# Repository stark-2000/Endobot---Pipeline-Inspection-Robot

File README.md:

Endobot 2.0, a tethered pipeline inspection robot which can detect leaks, corrosion and defects on pipelines as small as 4 inch up-to a depth of 300 meters and can withstand 5 bar underwater pressure.
It uses RS422 long distance data transfer protocol for camera feed & data transfer. The robot can be fully controlled from outside the pipeline using sophisticated controllers which enable 4 wheel drive and advanced transmission. 
Onboard IMU & Encoders enable accurate localisation & distance calculation of the robot. Realtime motor temp, indoor temp, pipeline leak sounds, current consumption, inclination calculation is all performed and displayed on a mini LCD screen.

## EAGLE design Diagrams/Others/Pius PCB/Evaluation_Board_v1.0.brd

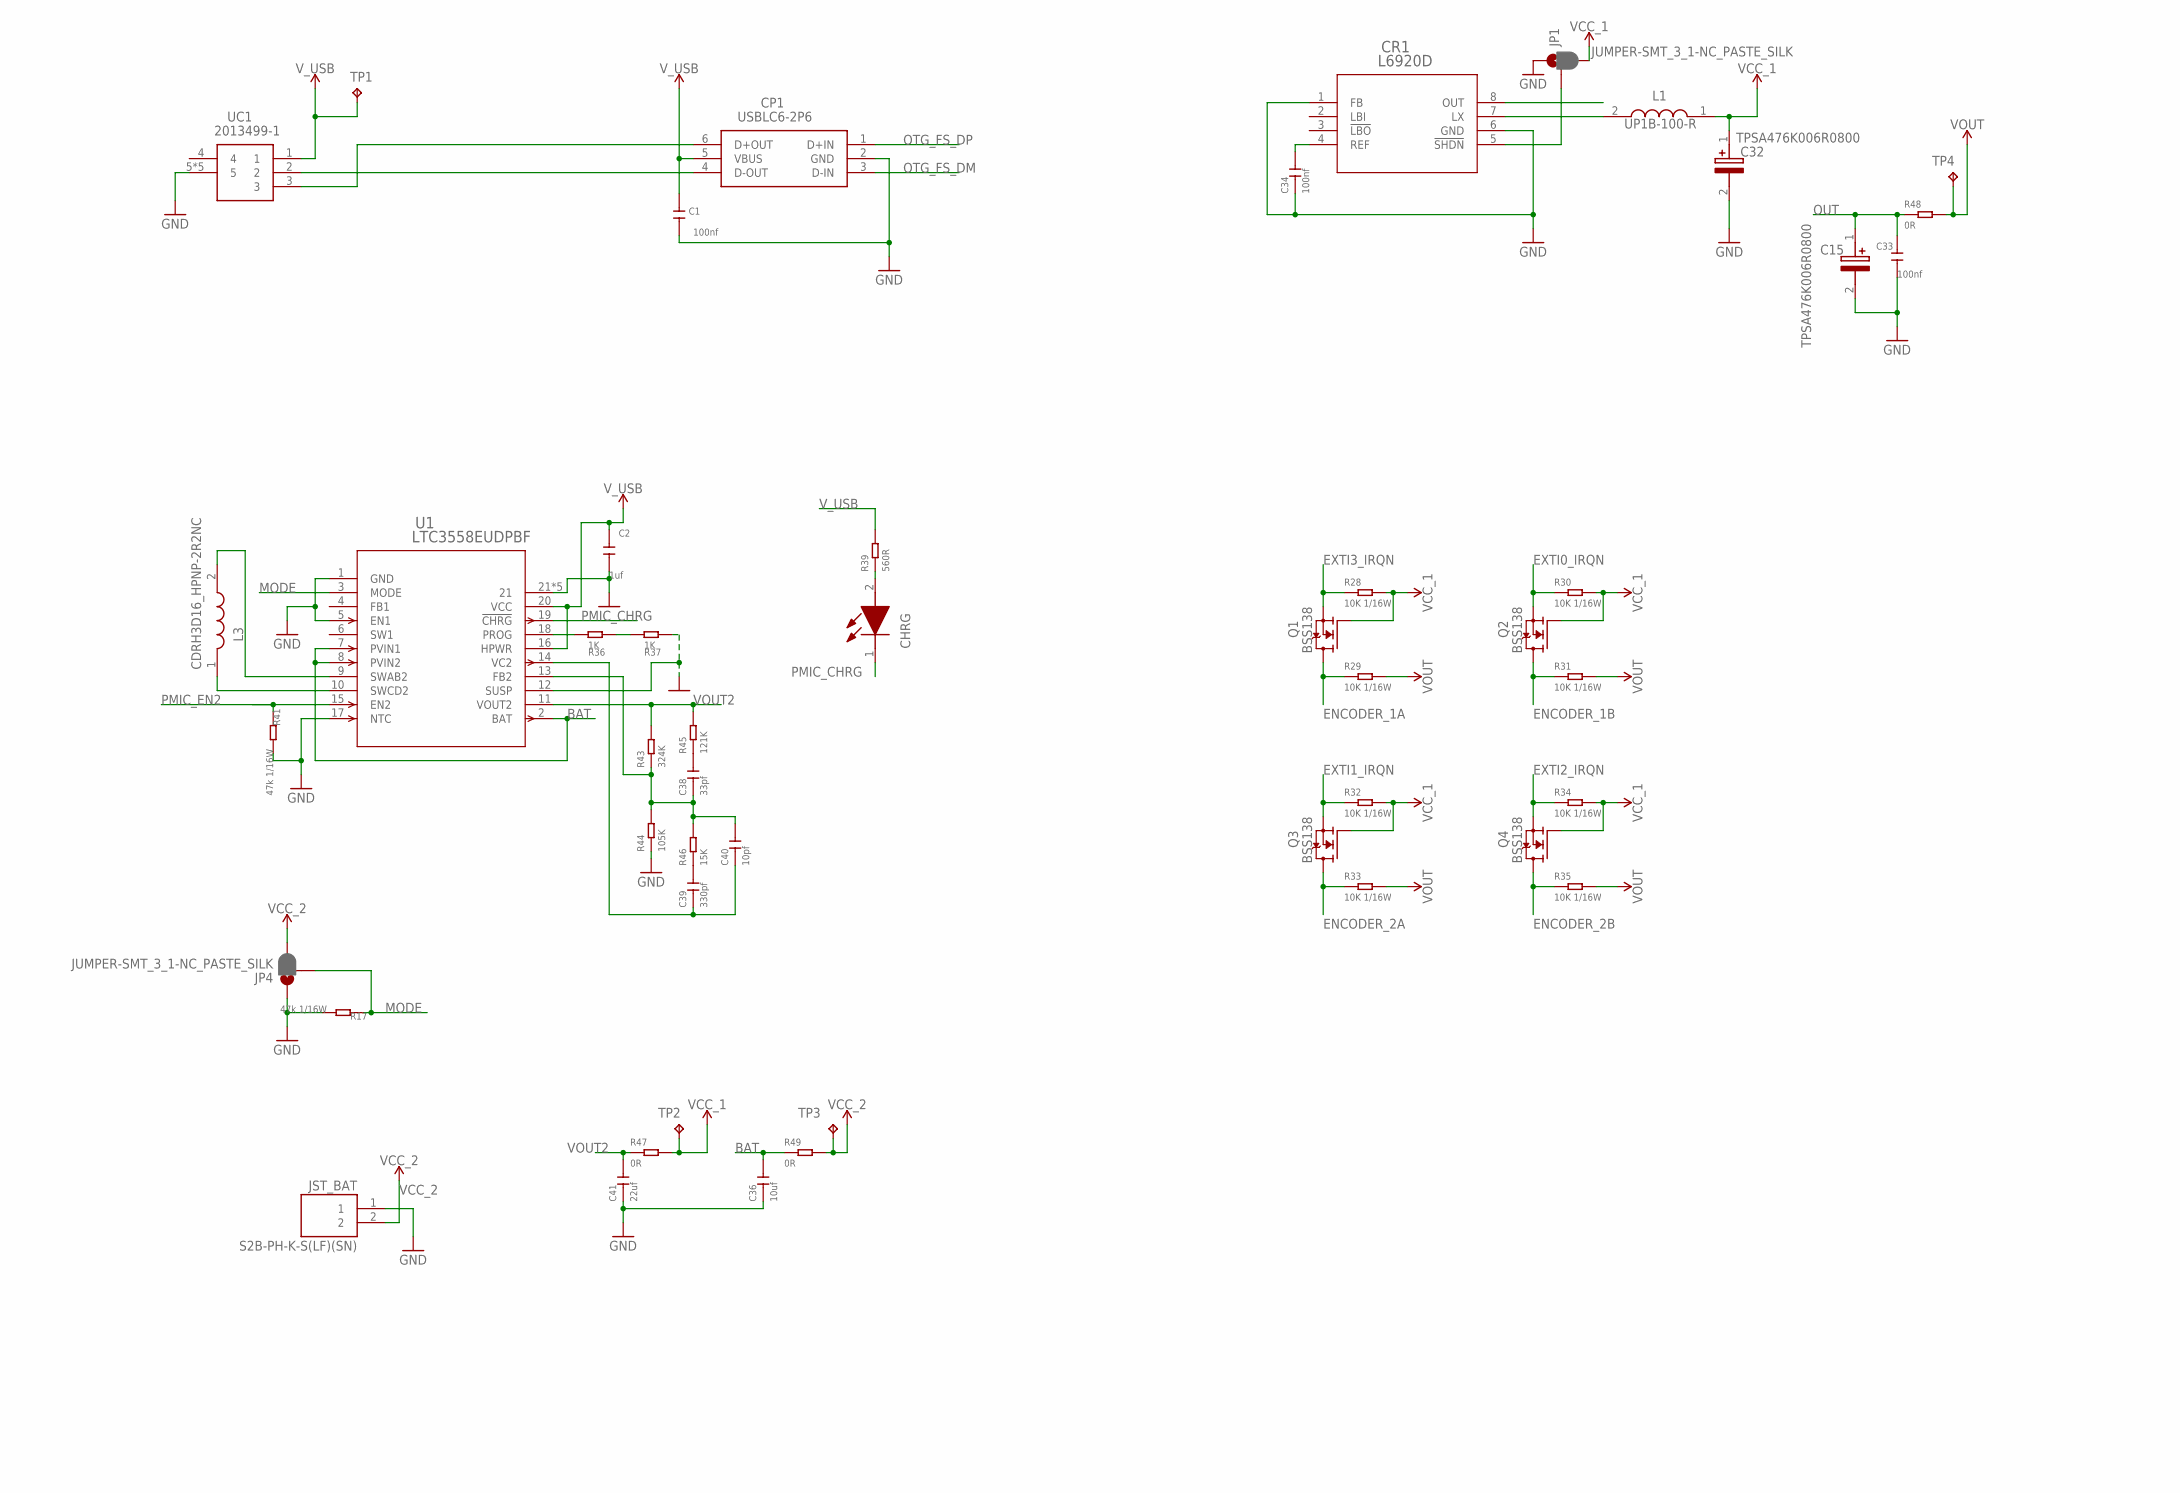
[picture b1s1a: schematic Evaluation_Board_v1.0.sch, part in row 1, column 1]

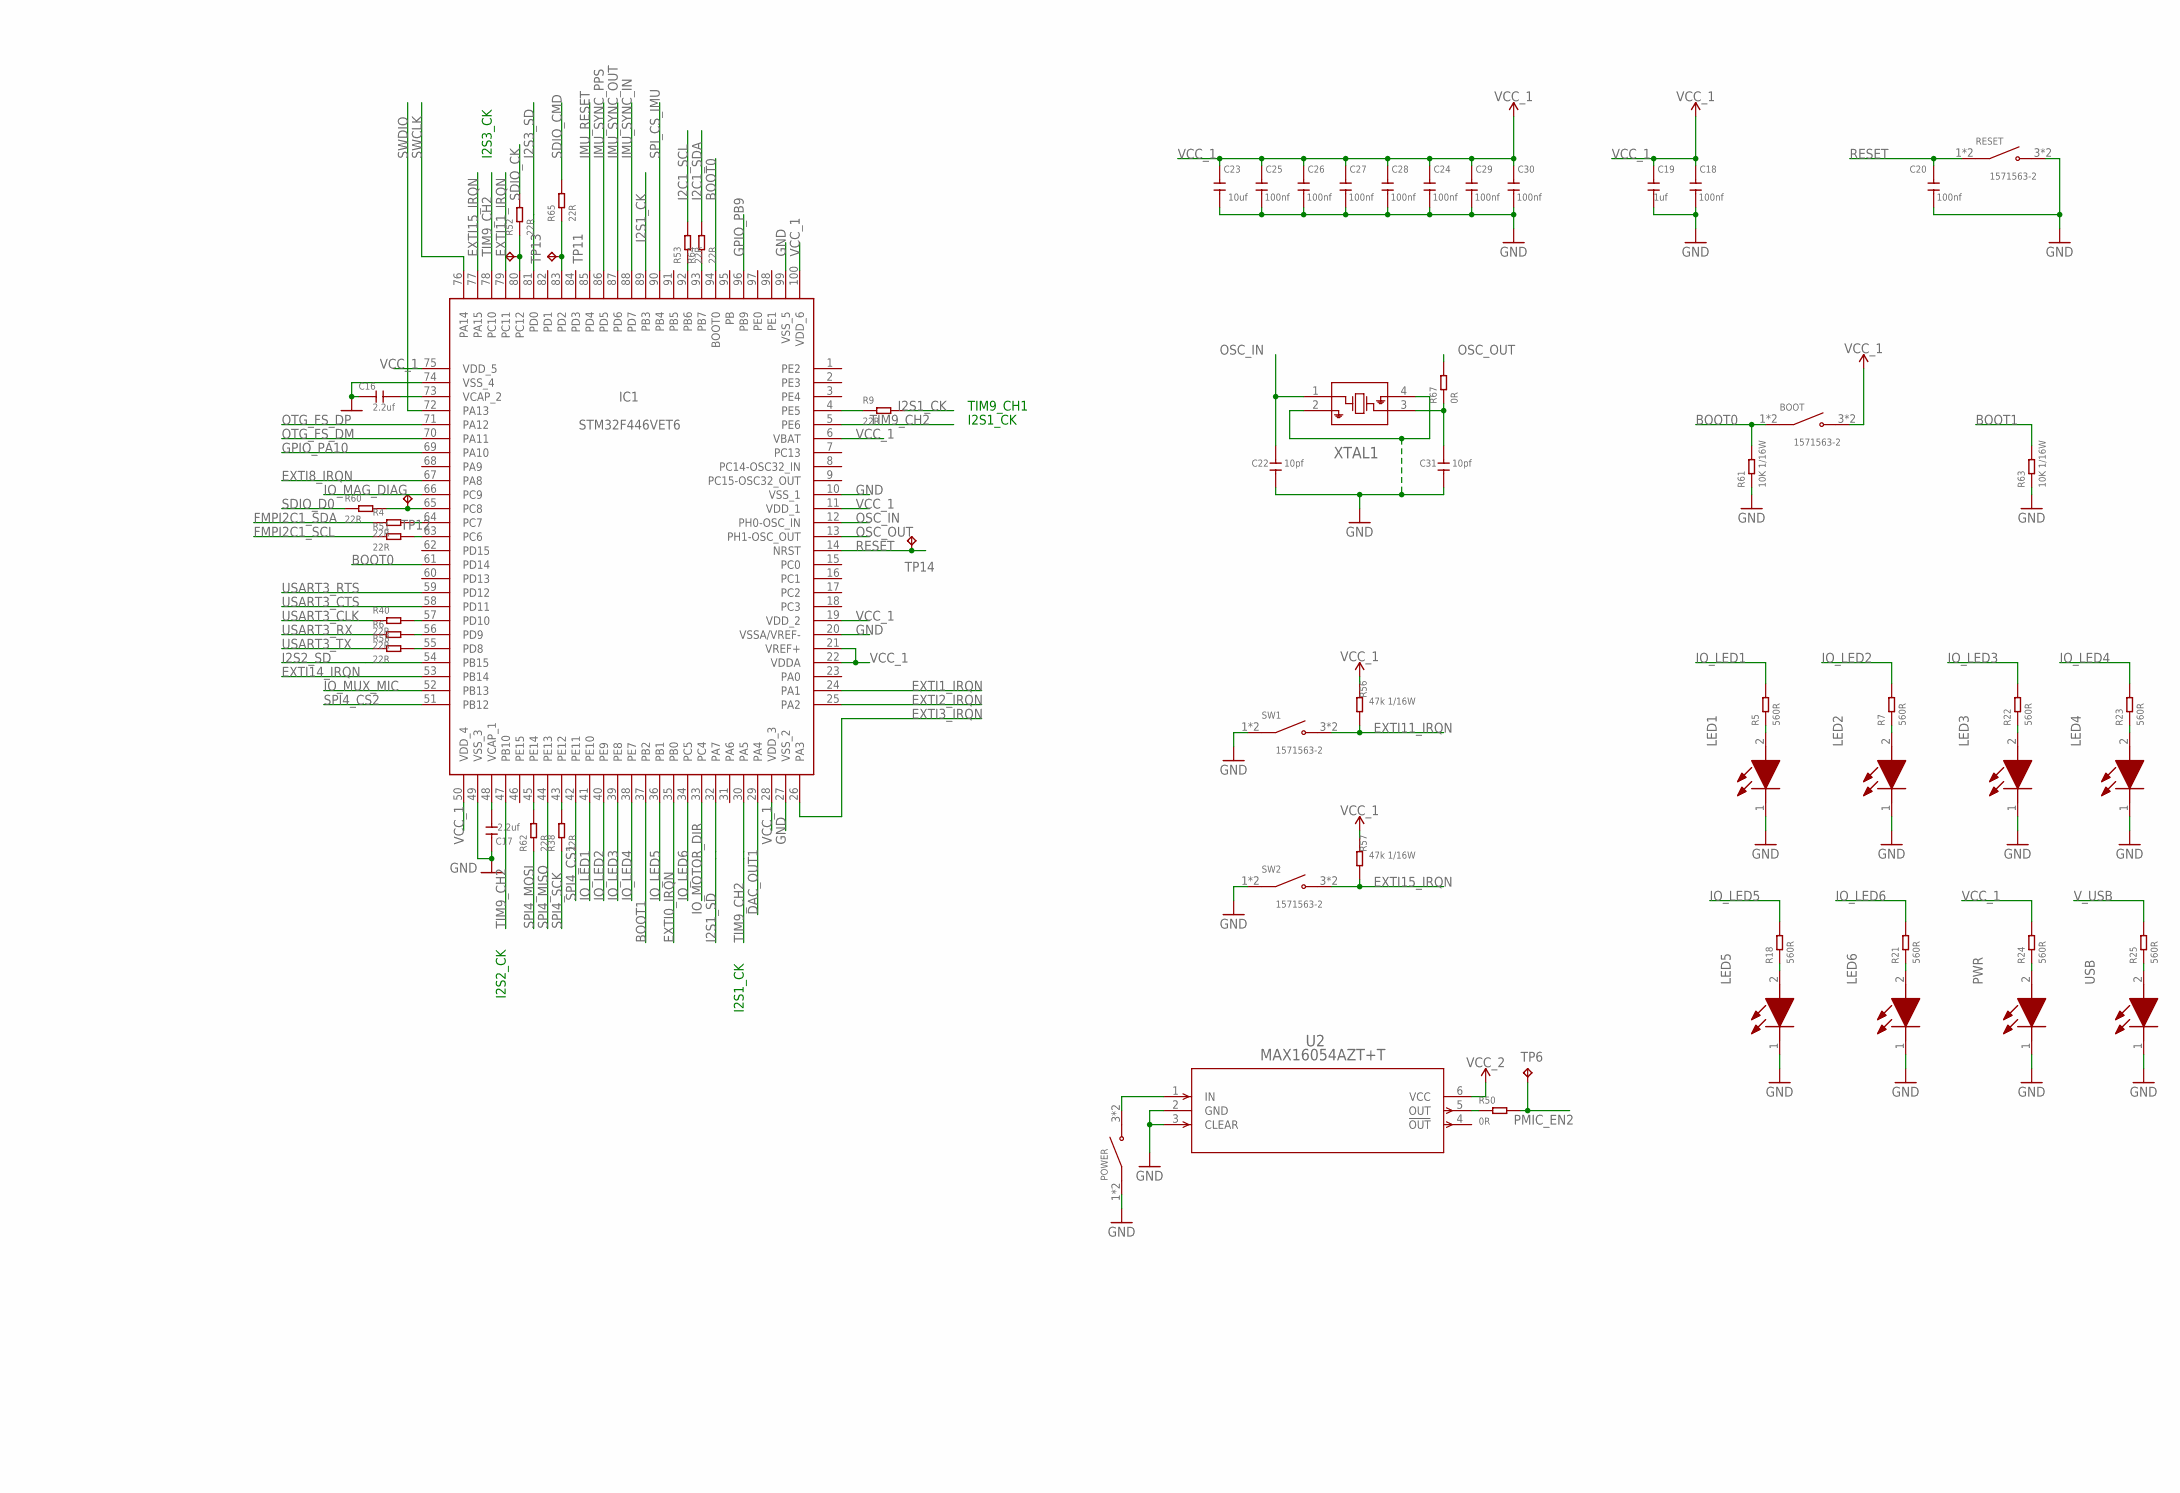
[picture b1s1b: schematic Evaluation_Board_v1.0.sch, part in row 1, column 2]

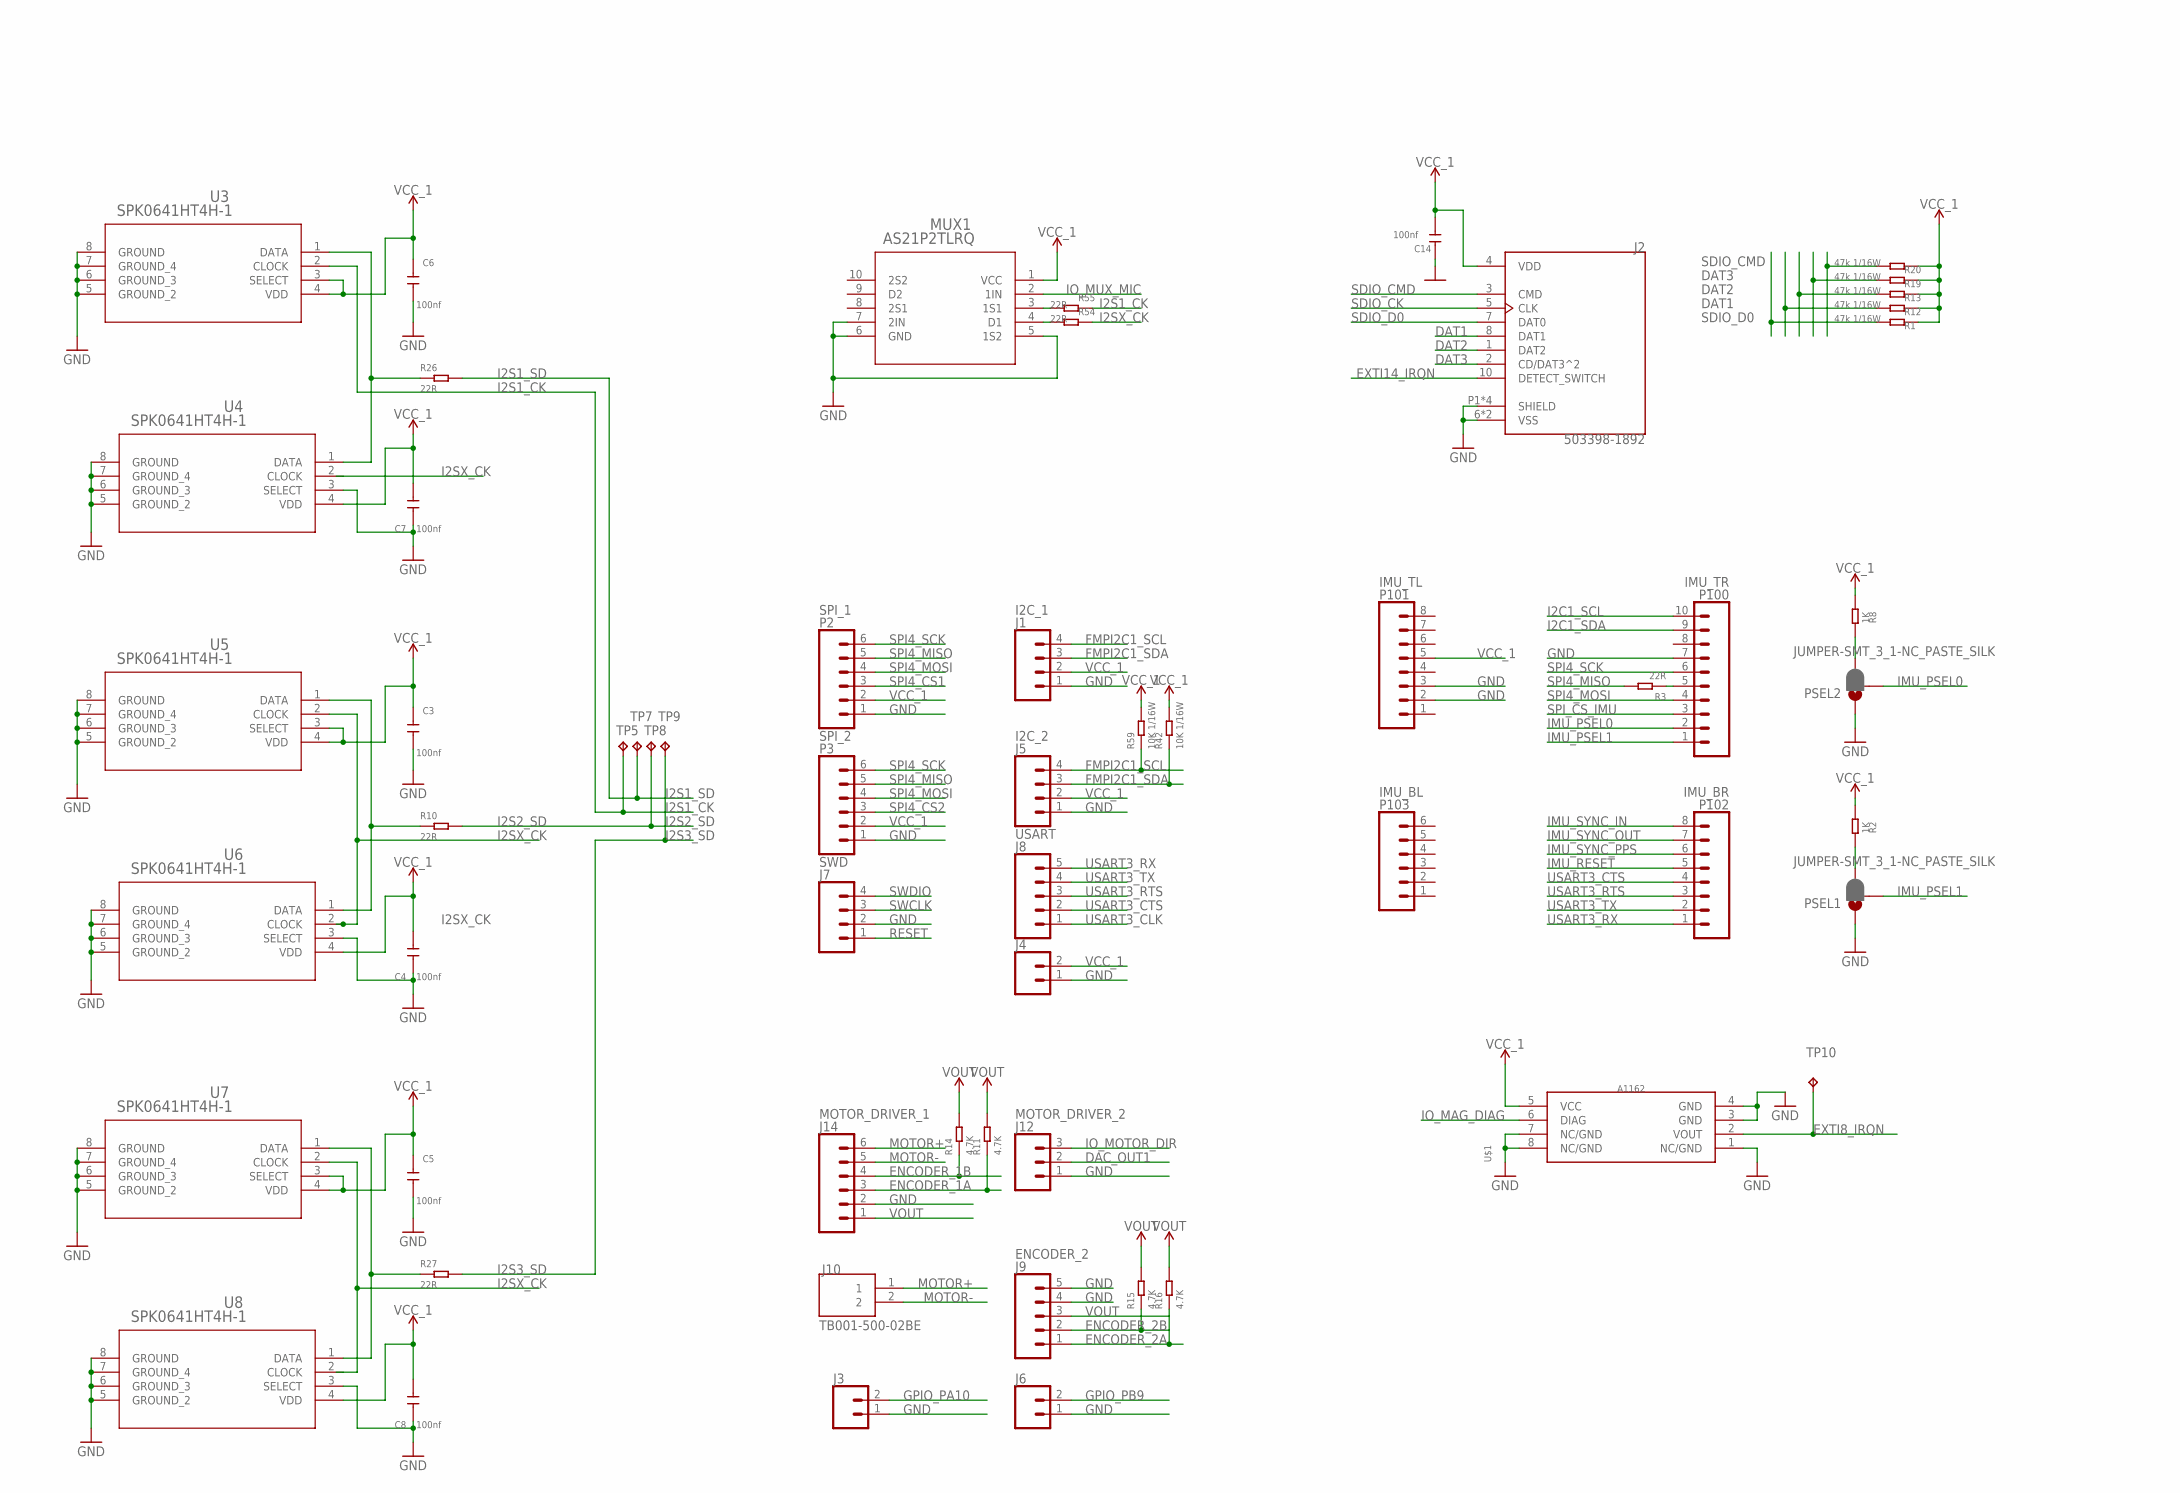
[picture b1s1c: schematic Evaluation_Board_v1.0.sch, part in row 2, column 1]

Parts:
BOOT: 1571563-2; SW_1571563-2
C1, C3, C4, C5, C6, C7, C8, C14, C18, C20, C24, C25, C26, C27, C28, C29, C30, C33, C34: 100nf; C0402
C2, C19: 1uf; C0402
C15, C32: TPSA476K006R0800; CAPPM3216X180N
C16, C17: 2.2uf; C0603
C22, C31, C40: 10pf; C0402
C23, C36: 10uf; C0603
C38: 33pf; C0402
C39: 330pf; C0402
C41: 22uf; C0805
CHRG: SML-P12MTT86R; LEDM106X25N
CP1: USBLC6-2P6; USBLC62P6
CR1: L6920D; TSSOP8_STM
IC1: STM32F446VET6; QFP50P1600X1600X160-100N
J1: I2C_1; 1X04
J2: 503398-1892; MOLEX_503398-1892
J3, J4, J6: CONN_02; 1X02
J5: I2C_2; 1X04
J7: SWD; 1X04
J8: USART; 1X05
J9: ENCODER_2; 1X05
J10: TB001-500-02BE; CUI_TB001-500-02BE
J12: MOTOR_DRIVER_2; 1X03
J14: MOTOR_DRIVER_1; MOLEX-1X6
JP1, JP4: JUMPER-SMT_3_1-NC_PASTE_SILK; SMT-JUMPER_3_1-NC_PASTE_SILK
JST_BAT: S2B-PH-K-S(LF)(SN); JST_S2B-PH-K-S(LF)(SN)
L1: UP1B-100-R; INDM9060X500N
L3: CDRH3D16_HPNP-2R2NC; CDRH3D16HPNP2R2NC
LED1, LED2, LED3, LED4, LED5, LED6: SML-P12MTT86R; LEDM106X25N
MUX1: AS21P2TLRQ; QFN10_1P8X1P4X0P5_STM
P2: SPI_1; 1X06
P3: SPI_2; 1X06
P100: IMU_TR; 1X10
P101: IMU_TL; 1X08
P102: IMU_BR; 1X08
P103: IMU_BL; 1X06
POWER: 1571563-2; SW_1571563-2
PSEL1, PSEL2: JUMPER-SMT_3_1-NC_PASTE_SILK; SMT-JUMPER_3_1-NC_PASTE_SILK
PWR: SML-P12MTT86R; LEDM106X25N
Q1, Q2, Q3, Q4: BSS138; SOT95P240X111-3N
R1, R12, R13, R17, R19, R20, R41, R56, R57: 47k 1/16W; R0402
R2, R8, R36, R37: 1K; R0603
R3, R4, R6, R9, R10, R26, R27, R38, R40, R51, R52, R53, R54, R55, R58, R60, R62, R64, R65: 22R; R0402
R5, R7, R18, R21, R22, R23, R24, R25, R39: 560R; R0603
R11, R14, R15, R16: 4.7K; R0402
R28, R29, R30, R31, R32, R33, R34, R35, R42, R59, R61, R63: 10K 1/16W; R0402
R43: 324K; R0603
R44: 105K; R0603
R45: 121K; R0603
R46: 15K; R0603
R47, R48, R49, R50: 0R; R0805
R67: 0R; R0402
RESET: 1571563-2; SW_1571563-2
SW1, SW2: 1571563-2; SW_1571563-2
TP1, TP2, TP3, TP4, TP5, TP6, TP7, TP8, TP9, TP10, TP11, TP12, TP13, TP14: TPB1,27; B1,27
U1: LTC3558EUDPBF; QFN-20_UD_LIT
U2: MAX16054AZT+T; 21-0114C_MXM
U3, U4, U5, U6, U7, U8: SPK0641HT4H-1; SPK0641HT4H-1_KNO
U$1: A1162; A1162-8
UC1: 2013499-1
USB: SML-P12MTT86R; LEDM106X25N
XTAL1: NX2520SA-16MHZ; NX2520SA_NDK

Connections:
BAT: C36.2, R49.1, U1.2 (BAT), U1.7 (PVIN1), U1.8 (PVIN2)
BOOT0: BOOT.1 (COM), BOOT.2 (COM), IC1.61 (PD14), IC1.94 (BOOT0), R61.2
BOOT1: IC1.37 (PB2), R63.2
DAC_OUT1: IC1.29 (PA4), J12.2
DAT1: J2.8 (DAT1), R12.1
DAT2: J2.1 (DAT2), R13.1
DAT3: J2.2 (CD/DAT3^2), R19.1
ENCODER_1A: J14.3, Q1.3 (D), R11.1, R29.1
ENCODER_1B: J14.4, Q2.3 (D), R14.1, R31.1
ENCODER_2A: J9.1, Q3.3 (D), R16.1, R33.1
ENCODER_2B: J9.2, Q4.3 (D), R15.1, R35.1
EXTI0_IRQN: IC1.35 (PB0), Q2.2 (S), R30.1
EXTI1_IRQN: IC1.24 (PA1), Q3.2 (S), R32.1
EXTI2_IRQN: IC1.25 (PA2), Q4.2 (S), R34.1
EXTI3_IRQN: IC1.26 (PA3), Q1.2 (S), R28.1
EXTI8_IRQN: IC1.67 (PA8), TP10.TP, U$1.2 (VOUT)
EXTI11_IRQN: IC1.79 (PC11), R56.1, SW1.3 (NO), SW1.4 (NO)
EXTI14_IRQN: IC1.53 (PB14), J2.10 (DETECT_SWITCH)
EXTI15_IRQN: IC1.77 (PA15), R57.1, SW2.3 (NO), SW2.4 (NO)
FMPI2C1_SCL: J1.4, J5.4, R51.1, R59.1
FMPI2C1_SDA: J1.3, J5.3, R4.1, R42.1
GND: C1.1, C2.1, C3.1, C4.1, C5.1, C6.1, C7.1, C8.1, C14.2, C15.2 (-), C16.1, C17.1, C18.1, C19.1, C20.1, C22.1, C23.1, C24.1, C25.1, C26.1, C27.1, C28.1, C29.1, C30.1, C31.1, C32.2 (-), C33.2, C34.1, C36.1, C41.1, CP1.2 (GND), CR1.1 (FB), CR1.6 (GND), IC1.10 (VSS_1), IC1.20 (VSSA/VREF-), IC1.27 (VSS_2), IC1.49 (VSS_3), IC1.74 (VSS_4), IC1.99 (VSS_5), J1.1, J2.6 (VSS), J2.9 (VSS), J2.P1 (SHIELD), J2.P2 (SHIELD), J2.P3 (SHIELD), J2.P4 (SHIELD), J3.1, J4.1, J5.1, J6.1, J7.2, J9.4, J9.5, J12.1, J14.2, JP1.1, JP4.1, JST_BAT.1, LED1.1 (K), LED2.1 (K), LED3.1 (K), LED4.1 (K), LED5.1 (K), LED6.1 (K), MUX1.5 (1S2), MUX1.6 (GND), MUX1.7 (2IN), P2.1, P3.1, P100.7, P101.2, P101.3, POWER.1 (COM), POWER.2 (COM), PSEL1.1, PSEL2.1, PWR.1 (K), R17.1, R37.2, R41.1, R44.1, R61.1, R63.1, RESET.3 (NO), RESET.4 (NO), SW1.1 (COM), SW1.2 (COM), SW2.1 (COM), SW2.2 (COM), U1.1 (GND), U1.5 (EN1), U1.12 (SUSP), U1.17 (NTC), U1.21, U1.P$1 (21), U1.P$2 (21), U1.P$3 (21), U1.P$4 (21), U2.2 (GND), U2.3 (CLEAR), U3.5 (GROUND_2), U3.6 (GROUND_3), U3.7 (GROUND_4), U3.8 (GROUND), U4.3 (SELECT), U4.5 (GROUND_2), U4.6 (GROUND_3), U4.7 (GROUND_4), U4.8 (GROUND), U5.5 (GROUND_2), U5.6 (GROUND_3), U5.7 (GROUND_4), U5.8 (GROUND), U6.3 (SELECT), U6.5 (GROUND_2), U6.6 (GROUND_3), U6.7 (GROUND_4), U6.8 (GROUND), U7.5 (GROUND_2), U7.6 (GROUND_3), U7.7 (GROUND_4), U7.8 (GROUND), U8.3 (SELECT), U8.5 (GROUND_2), U8.6 (GROUND_3), U8.7 (GROUND_4), U8.8 (GROUND), U$1.1 (NC/GND), U$1.3 (GND), U$1.4 (GND), U$1.7 (NC/GND), U$1.8 (NC/GND), UC1.5, UC1.6 (5), UC1.7 (5), UC1.8 (5), UC1.9 (5), USB.1 (K), XTAL1.2, XTAL1.4
GPIO_PA10: IC1.69 (PA10), J3.2
GPIO_PB9: IC1.96 (PB9), J6.2
I2C1_SCL: P100.10, R53.2
I2C1_SDA: P100.9, R64.2
I2S1_CK: IC1.4 (PE5), IC1.89 (PB3), R9.1, R9.2, R55.2, TP5.TP, U3.2 (CLOCK)
I2S1_SD: IC1.32 (PA7), R26.2, TP7.TP
I2S2_SD: IC1.54 (PB15), R10.2, TP8.TP
I2S3_SD: IC1.81 (PD0), R27.2, TP9.TP
I2SX_CK: R54.2, U4.2 (CLOCK), U5.2 (CLOCK), U6.2 (CLOCK), U7.2 (CLOCK), U8.2 (CLOCK)
IMU_PSEL0: P100.2, PSEL2.2
IMU_PSEL1: P100.1, PSEL1.2
IMU_RESET: IC1.85 (PD4), P102.5
IMU_SYNC_IN: IC1.88 (PD7), P102.8
IMU_SYNC_OUT: IC1.87 (PD6), P102.7
IMU_SYNC_PPS: IC1.86 (PD5), P102.6
IO_LED1: IC1.41 (PE10), R5.2
IO_LED2: IC1.40 (PE9), R7.2
IO_LED3: IC1.39 (PE8), R22.2
IO_LED4: IC1.38 (PE7), R23.2
IO_LED5: IC1.36 (PB1), R18.2
IO_LED6: IC1.34 (PC5), R21.2
IO_MAG_DIAG: IC1.66 (PC9), U$1.6 (DIAG)
IO_MOTOR_DIR: IC1.33 (PC4), J12.3
IO_MUX_MIC: IC1.52 (PB13), MUX1.2 (1IN)
MODE: JP4.2, R17.2, U1.3 (MODE)
MOTOR+: J10.1, J14.6
MOTOR-: J10.2, J14.5
unnamed: C34.2, CR1.4 (REF)
unnamed: CR1.7 (LX), L1.2
unnamed: CP1.4 (D-OUT), UC1.2
unnamed: CP1.6 (D+OUT), UC1.3
unnamed: R36.1, U1.18 (PROG)
unnamed: R36.2, R37.1
unnamed: CHRG.2 (A), R39.1
unnamed: CR1.5 (!SHDN), JP1.2
unnamed: C38.2, R45.1
unnamed: C17.2, IC1.48 (VCAP_1)
unnamed: R50.1, U2.5 (OUT)
unnamed: C38.1, C40.2, R43.1, R44.2, R46.2, U1.13 (FB2)
unnamed: C39.2, R46.1
unnamed: C16.2, IC1.73 (VCAP_2)
unnamed: POWER.3 (NO), POWER.4 (NO), U2.1 (IN)
unnamed: PSEL1.3, R2.1
unnamed: MUX1.4 (D1), R54.1
unnamed: L3.1, U1.10 (SWCD2)
unnamed: C31.2, R67.1, XTAL1.3
unnamed: PSEL2.3, R8.1
unnamed: C39.1, C40.1, U1.14 (VC2)
unnamed: L3.2, U1.9 (SWAB2)
unnamed: LED1.2 (A), R5.1
unnamed: MUX1.3 (1S1), R55.1
unnamed: LED2.2 (A), R7.1
unnamed: IC1.63 (PC6), R51.2
unnamed: LED5.2 (A), R18.1
unnamed: IC1.57 (PD10), R40.2
unnamed: LED6.2 (A), R21.1
unnamed: IC1.43 (PE12), R38.2
unnamed: LED3.2 (A), R22.1
unnamed: R10.1, U5.1 (DATA), U6.1 (DATA)
unnamed: LED4.2 (A), R23.1
unnamed: IC1.80 (PC12), R52.1, TP13.TP
unnamed: PWR.2 (A), R24.1
unnamed: IC1.92 (PB6), R53.1
unnamed: R25.1, USB.2 (A)
unnamed: IC1.64 (PC7), R4.2
unnamed: IC1.56 (PD9), R6.2
unnamed: IC1.55 (PD8), R58.2
unnamed: P100.5, R3.1
unnamed: IC1.65 (PC8), R60.2, TP12.TP
unnamed: R27.1, U7.1 (DATA), U8.1 (DATA)
unnamed: IC1.45 (PE14), R62.2
unnamed: IC1.93 (PB7), R64.1
unnamed: IC1.83 (PD2), R65.1, TP11.TP
unnamed: R26.1, U3.1 (DATA), U4.1 (DATA)
OSC_IN: C22.2, IC1.12 (PH0-OSC_IN), XTAL1.1
OSC_OUT: IC1.13 (PH1-OSC_OUT), R67.2
OTG_FS_DM: CP1.3 (D-IN), IC1.70 (PA11)
OTG_FS_DP: CP1.1 (D+IN), IC1.71 (PA12)
OUT: C15.1 (+), C33.1, CR1.8 (OUT), R48.1
PMIC_CHRG: CHRG.1 (K), U1.19 (!CHRG)
PMIC_EN2: R41.2, R50.2, TP6.TP, U1.15 (EN2)
RESET: C20.2, IC1.14 (NRST), J7.1, RESET.1 (COM), RESET.2 (COM), TP14.TP
SDIO_CK: J2.5 (CLK), R52.2
SDIO_CMD: J2.3 (CMD), R20.1, R65.2
SDIO_D0: J2.7 (DAT0), R1.1, R60.1
SPI4_CS1: IC1.42 (PE11), P2.3
SPI4_CS2: IC1.51 (PB12), P3.3
SPI4_MISO: IC1.44 (PE13), P2.5, P3.5, R3.2
SPI4_MOSI: P2.4, P3.4, P100.4, R62.1
SPI4_SCK: P2.6, P3.6, P100.6, R38.1
SPI_CS_IMU: IC1.90 (PB4), P100.3
SWCLK: IC1.76 (PA14), J7.3
SWDIO: IC1.72 (PA13), J7.4
TIM9_CH2: IC1.5 (PE6), IC1.30 (PA5), IC1.47 (PB10), IC1.78 (PC10)
USART3_CLK: J8.1, R40.1
USART3_CTS: IC1.58 (PD11), J8.2, P102.4
USART3_RTS: IC1.59 (PD12), J8.3, P102.3
USART3_RX: J8.5, P102.1, R6.1
USART3_TX: J8.4, P102.2, R58.1
VCC_1: BOOT.3 (NO), BOOT.4 (NO), C3.2, C4.2, C5.2, C6.2, C7.2, C8.2, C14.1, C18.2, C19.2, C23.2, C24.2, C25.2, C26.2, C27.2, C28.2, C29.2, C30.2, C32.1 (+), IC1.6 (VBAT), IC1.11 (VDD_1), IC1.19 (VDD_2), IC1.21 (VREF+), IC1.22 (VDDA), IC1.28 (VDD_3), IC1.50 (VDD_4), IC1.75 (VDD_5), IC1.100 (VDD_6), J1.2, J2.4 (VDD), J4.2, J5.2, JP1.3, L1.1, MUX1.1 (VCC), P2.2, P3.2, P101.5, Q1.1 (G), Q2.1 (G), Q3.1 (G), Q4.1 (G), R1.2, R2.2, R8.2, R12.2, R13.2, R19.2, R20.2, R24.2, R28.2, R30.2, R32.2, R34.2, R42.2, R47.2, R56.2, R57.2, R59.2, TP2.TP, U3.3 (SELECT), U3.4 (VDD), U4.4 (VDD), U5.3 (SELECT), U5.4 (VDD), U6.4 (VDD), U7.3 (SELECT), U7.4 (VDD), U8.4 (VDD), U$1.5 (VCC)
VCC_2: JP4.3, JST_BAT.2, R49.2, TP3.TP, U2.6 (VCC)
VOUT: J9.3, J14.1, R11.2, R14.2, R15.2, R16.2, R29.2, R31.2, R33.2, R35.2, R48.2, TP4.TP
VOUT2: C41.2, R43.2, R45.2, R47.1, U1.11 (VOUT2)
V_USB: C1.2, C2.2, CP1.5 (VBUS), R25.2, R39.2, TP1.TP, U1.16 (HPWR), U1.20 (VCC), UC1.1

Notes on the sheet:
I2S1_CK
TIM9_CH1
I2S3_CK
I2S2_CK

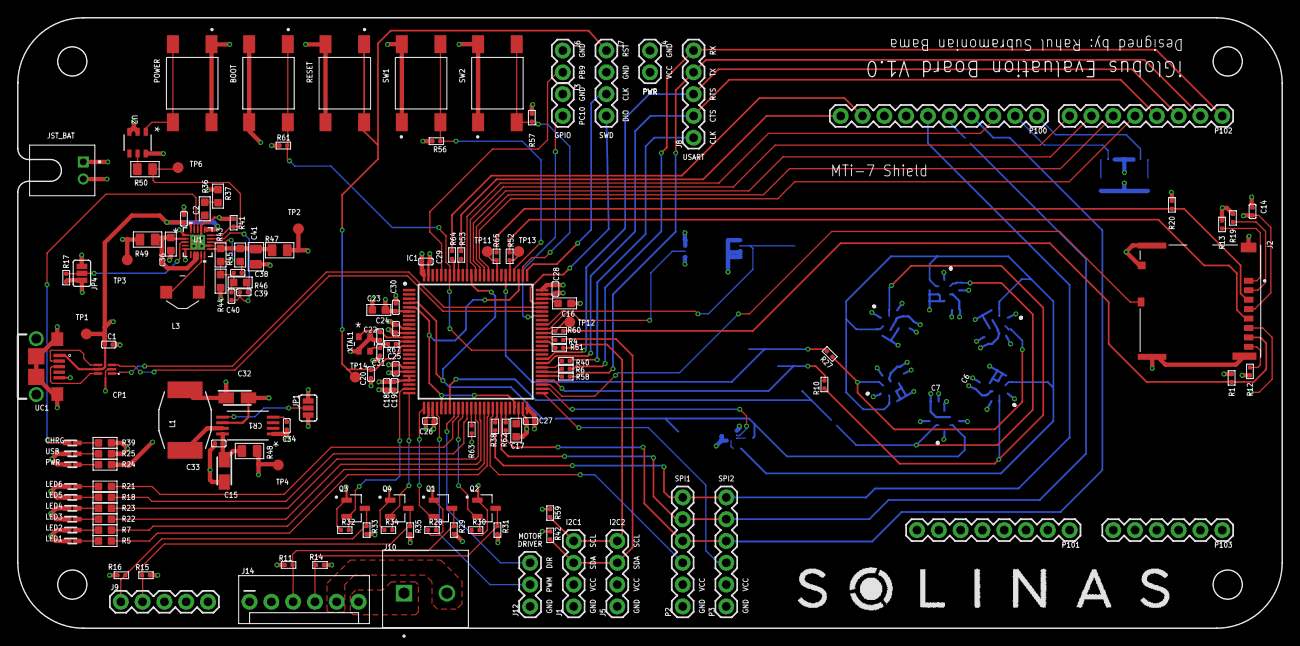
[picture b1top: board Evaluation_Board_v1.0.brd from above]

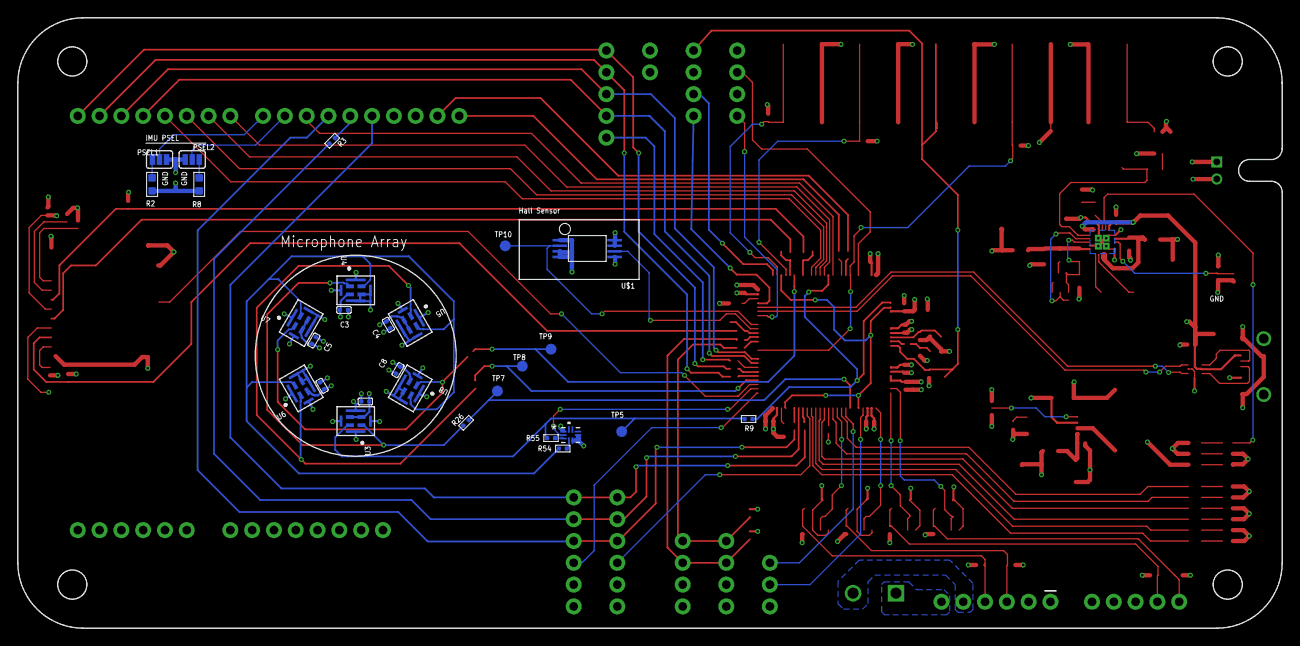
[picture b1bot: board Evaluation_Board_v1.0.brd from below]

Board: 4 copper layers, 147.3 x 71.1 mm, 172 parts (28 on the bottom side), 126 nets.

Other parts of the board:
U$2: SOLINAS-LOGO

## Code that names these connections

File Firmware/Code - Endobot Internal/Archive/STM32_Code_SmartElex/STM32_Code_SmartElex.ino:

//STM32 Board with SmartElex Motor Driver - basic and RS422

HardwareSerial Serial1(USART3);

String buf;

//Motor Driver Pins:
#define DIR1 PE12
#define PWM1 PE13
#define DIR2 PE11
#define PWM2 PE14

//Endobot LED Pin:
#define TIP PB12


void setup()
{
  Serial1.setRx(PD9);
  Serial1.setTx(PD8);
  Serial1.begin (9600);
  
  pinMode(DIR1, OUTPUT);
  pinMode(DIR2, OUTPUT);
  pinMode(PWM1, OUTPUT);
  pinMode(PWM2, OUTPUT);
  pinMode(TIP, OUTPUT);
}


void loop() 
{ 
   
   int a = 0, b = 0, c = 0, sh = 0, sh1 = 0, sh2 = 0;
   char x[10] = "0", y[10] = "0", z[10] = "0";
   int h = 0;
   int FB, LR, LEDpot;

   if (Serial.available ())                  // if any data came to the port
   {
       delay (5);                            // wait a bit for the entire data packet to be accepted by the port
       buf = Serial.readStringUntil('\n');   //Read serial data until null character
       Serial.println(buf);                  //Print data on serial monitor
   }

   a = buf[0] - '0';
   //Serial.println(a);
   
   b = buf[1] - '0';
   //Serial.println(b);
   
   c = buf[2] - '0';
   //Serial.println(c);
   //delay(1000);

   
   for(int j = 3; j<= (a+2); j++)
   {
     x[h] = buf[j];
     h++;
   }
   h = 0;
   //Serial.println(x);
   FB = atoi(x);                    //Forward/Backward Joystick Value
   //Serial.println(FB);
   
   
   for(int j = (3+a); j<= (b+a+2); j++)
   {
     y[h] = buf[j];
     h++;
   }
   h = 0;
   //Serial.println(y);
   LR = atoi(y);                    //Left/Right Joystick Value
   //Serial.println(LR);

   
   for(int j = (3+a+b); j<= (c+b+a+2); j++)
   {
     z[h] = buf[j];
     h++;
   }
   //Serial.println(z);
   LEDpot = atoi(z);                //Endobot LED Pot Value
   //Serial.println(LEDpot);
   

   sh = buf[a+b+c+3] - '0';
   //Serial.println(sh);
   sh1 = buf[a+b+c+4] - '0';
   //Serial.println(sh1);
   sh2 = buf[a+b+c+5] - '0';
   //Serial.println(sh2);


   int mappedF = map(FB, 540, 1023, 0, 255);  
   //Serial.println(mappedF);
   int mappedB = map(FB, 500, 70, 0, 255);
   //Serial.println(mappedB);
   int mappedL = map(LR, 490, 192, 0, 255);
   //Serial.println(mappedL);
   int mappedR = map(LR, 520, 1023, 0, 255); 
   //Serial.println(mappedR);
   int mappedz = map(LEDpot, 0, 1023, 0, 255);

   if(sh == 0)
   {
     analogWrite(TIP, mappedz);
   }
    
   if(FB > 540 && (LR >= 490 && LR <= 520) && (sh1 == 1 && sh2 == 1)) //Forward Movement
   {
     analogWrite(PWM1, mappedF);
     analogWrite(PWM2, mappedF);
     digitalWrite(DIR1, HIGH);
     digitalWrite(DIR2, LOW);
   }

   else if(FB < 500 && (LR >= 490 && LR <= 520) && (sh1 == 1 && sh2 == 1)) //Reverse Movement
   {
     analogWrite(PWM1, mappedB);
     analogWrite(PWM2, mappedB);
     digitalWrite(DIR1, LOW);
     digitalWrite(DIR2, HIGH);
   }

   if(LR > 520 && (FB >= 500 && FB <= 540) && (sh1 == 1 && sh2 == 1)) //Right Turn
   {
     analogWrite(PWM1, 180);
     analogWrite(PWM2, 180);
     digitalWrite(DIR1, LOW);
     digitalWrite(DIR2, LOW);
   }

   else if(LR < 490 && (FB >= 500 && FB <= 540) && (sh1 == 1 && sh2 == 1)) //Left Turn
   {
     analogWrite(PWM1, 180);
     analogWrite(PWM2, 180);
     digitalWrite(DIR1, HIGH);
     digitalWrite(DIR2, HIGH);
   }

   if((sh1 == 0 && sh2 == 1) && (FB >= 500 && FB <= 540) && (LR >= 490 && LR <= 520)) //Forward Switch
   {
     analogWrite(PWM1, 255);
     analogWrite(PWM2, 255);
     digitalWrite(DIR1, HIGH);
     digitalWrite(DIR2, LOW);
   }
   
   else if((sh1 == 1 && sh2 == 0) && (FB >= 500 && FB <= 540) && (LR >= 490 && LR <= 520)) //Backward Switch
   {
     analogWrite(PWM1, 255);
     analogWrite(PWM2, 255);
     digitalWrite(DIR1, LOW);
     digitalWrite(DIR2, HIGH);
   }

   if((LR >= 490 && LR <= 520) && (FB >= 500 && FB <= 540) && ((sh1 == 1 && sh2 == 1) || (sh1 == 0 && sh2 == 0))) //Idle Condition
   {
     analogWrite(PWM1, 0);
     analogWrite(PWM2, 0);
   }

}

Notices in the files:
parts and their libraries:
SparkFun-Connectors: Licensing: Creative Commons ShareAlike 4.0 International - https://creativecommons.org/licenses/by-sa/4.0
COPYRIGHT: Copyright (C) 2018 Accelerated Designs. All rights reserved
